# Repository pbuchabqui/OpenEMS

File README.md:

# OpenEMS

ECU para motores a combustao interna, focada no STM32H562RGT6 (Cortex-M33, C++17). Prioriza baixa latencia, baixo jitter e previsibilidade temporal para injecao, ignicao, sensores e calibracao.

Regras de codigo, gates de qualidade e errata: ver `CLAUDE.md`.

## Build

```bash
make firmware     # .elf/.hex/.bin em /tmp/openems-build
make host-test    # regressao no PC
make ci-local     # todos os gates antes de merge
make clean
```

## Instalacao no motor

Pelo dashboard proprio (`tools/openems_dash`, aba **Install**), com guia passo a passo; alternativa: TunerStudio com `tools/ts/openems.ini`.

## Documentacao

| Documento | Conteudo |
|---|---|
| `docs/bench_test_manual.md` | Teste de bancada na WeAct VGT6, sem atuadores |
| `docs/bench_report_template.md` | Modelo do relatório de bancada (preencher durante o ensaio) |
| `docs/hw/README.md` | Hardware e pinout |
| `docs/wiring_diagram.md` | Esquematicos eletricos |
| `docs/ROADMAP.md` | Backlog, progresso e histórico do que foi concluído |
| `docs/datalog.md` | Datalog em cartão SD (VGT6): formato, anel e ferramentas |
| `docs/nn_viabilidade.md` | Estudo: redes neurais no STM32H562 (X-τ, STFT, PID) |
| `docs/guia_instalacao.md` | Guia de instalação no motor (10 passos) |
| `docs/arquitetura.md` | Camadas, regras e contratos entre elas |
| `docs/pipeline_motor.md` | Captura CKP/CMP, combustível, ignição, scheduling, ADC, comunicação |
| `docs/errata_stm32h562.md` | Errata ES0565 e impactos no projeto |
| `docs/qualidade_e_testes.md` | Gates locais, layout dos testes host, segredos |
| `docs/mvp_bancada.md` | Definição de pronto da bancada, frames CAN, ETB, X-τ |
| `docs/estado_e_hardening.md` | Estado atual, hardening feito e pinout por placa |
| `docs/fueling_system.md`, `closed_loop_fuel.md`, `idle_system.md`, `ignition_system.md`, `protection_system.md`, `output_contract.md` | Subsistemas |

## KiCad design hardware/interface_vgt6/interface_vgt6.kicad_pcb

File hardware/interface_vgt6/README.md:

# Carrier VGT6 (`interface_vgt6/`)

> **Status:** vigente · validado 2026-11-23 (esquemático gerado e conferido com `kicad-cli` 10.0.7; sem PCB)

Esquemático KiCad 10 de 5 folhas (alimentação, saídas INJ/IGN, ETB e auxiliares, entradas, CAN e headers) da carrier que recebe a WeAct H562 VGT6. Especificação: `docs/hw/interface_vgt6.md` e `docs/hw/interface_vgt6_nets.md`. Abra `interface_vgt6.kicad_pro` no KiCad.

## Arquivos

- `interface_vgt6.kicad_sch` (raiz) e `power`, `outputs`, `etb_aux`, `inputs`, `comms` (`.kicad_sch`).
- `OpenEMS.kicad_sym` e `sym-lib-table`: símbolos do MAX9924 e do TPS2553, que a biblioteca oficial não tem.
- `gen/build.py`, `gen/kicadgen.py`: gerador.

## Regenerar

`python3 hardware/interface_vgt6/gen/build.py`. **O gerador é de uma passada**: ele reescreve todos os `.kicad_sch`, então depois de editar no KiCad não rode de novo sobre os mesmos arquivos.

## Conferir

```bash
kicad-cli sch erc hardware/interface_vgt6/interface_vgt6.kicad_sch
python3 tools/interface_netcheck.py
```

O `interface_netcheck.py` compara os pinos de P1/P2 da netlist com `docs/hw/interface_vgt6_nets.md` e `docs/hw/weact_h562_schematic.md`, e exige `PGND` e `SGND` separadas.

## Em aberto

Footprints, valores e posições dos componentes ainda são de projeto; não há PCB nem BOM fechada.

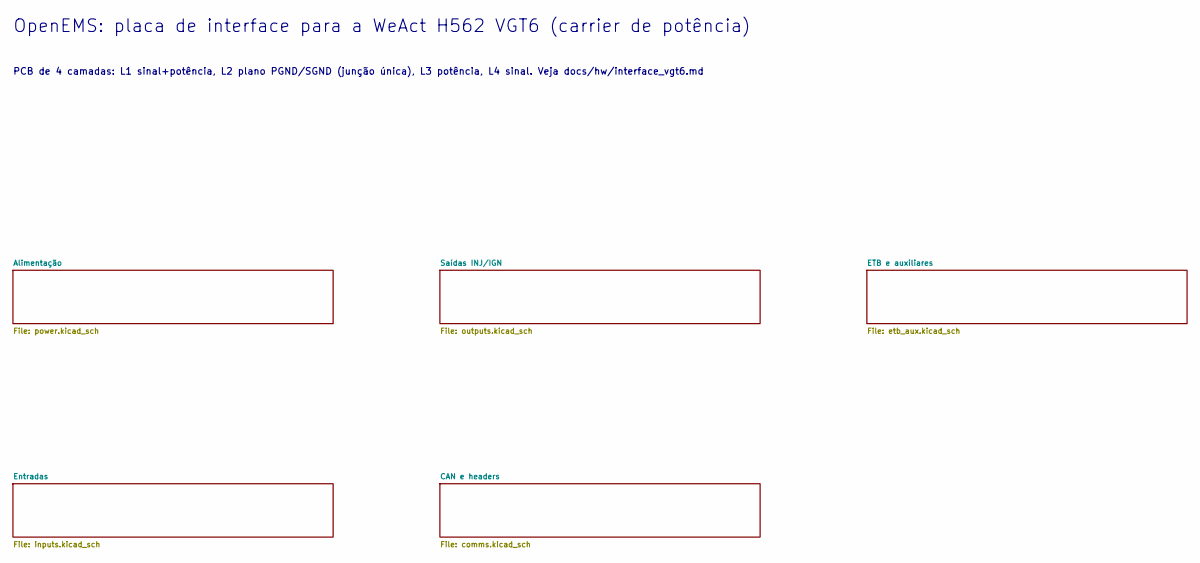
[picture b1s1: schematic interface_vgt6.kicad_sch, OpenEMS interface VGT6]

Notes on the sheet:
OpenEMS: placa de interface para a WeAct H562 VGT6 (carrier de potência)
PCB de 4 camadas: L1 sinal+potência, L2 plano PGND/SGND (junção única), L3 potência, L4 sinal. Veja docs/hw/interface_vgt6.md

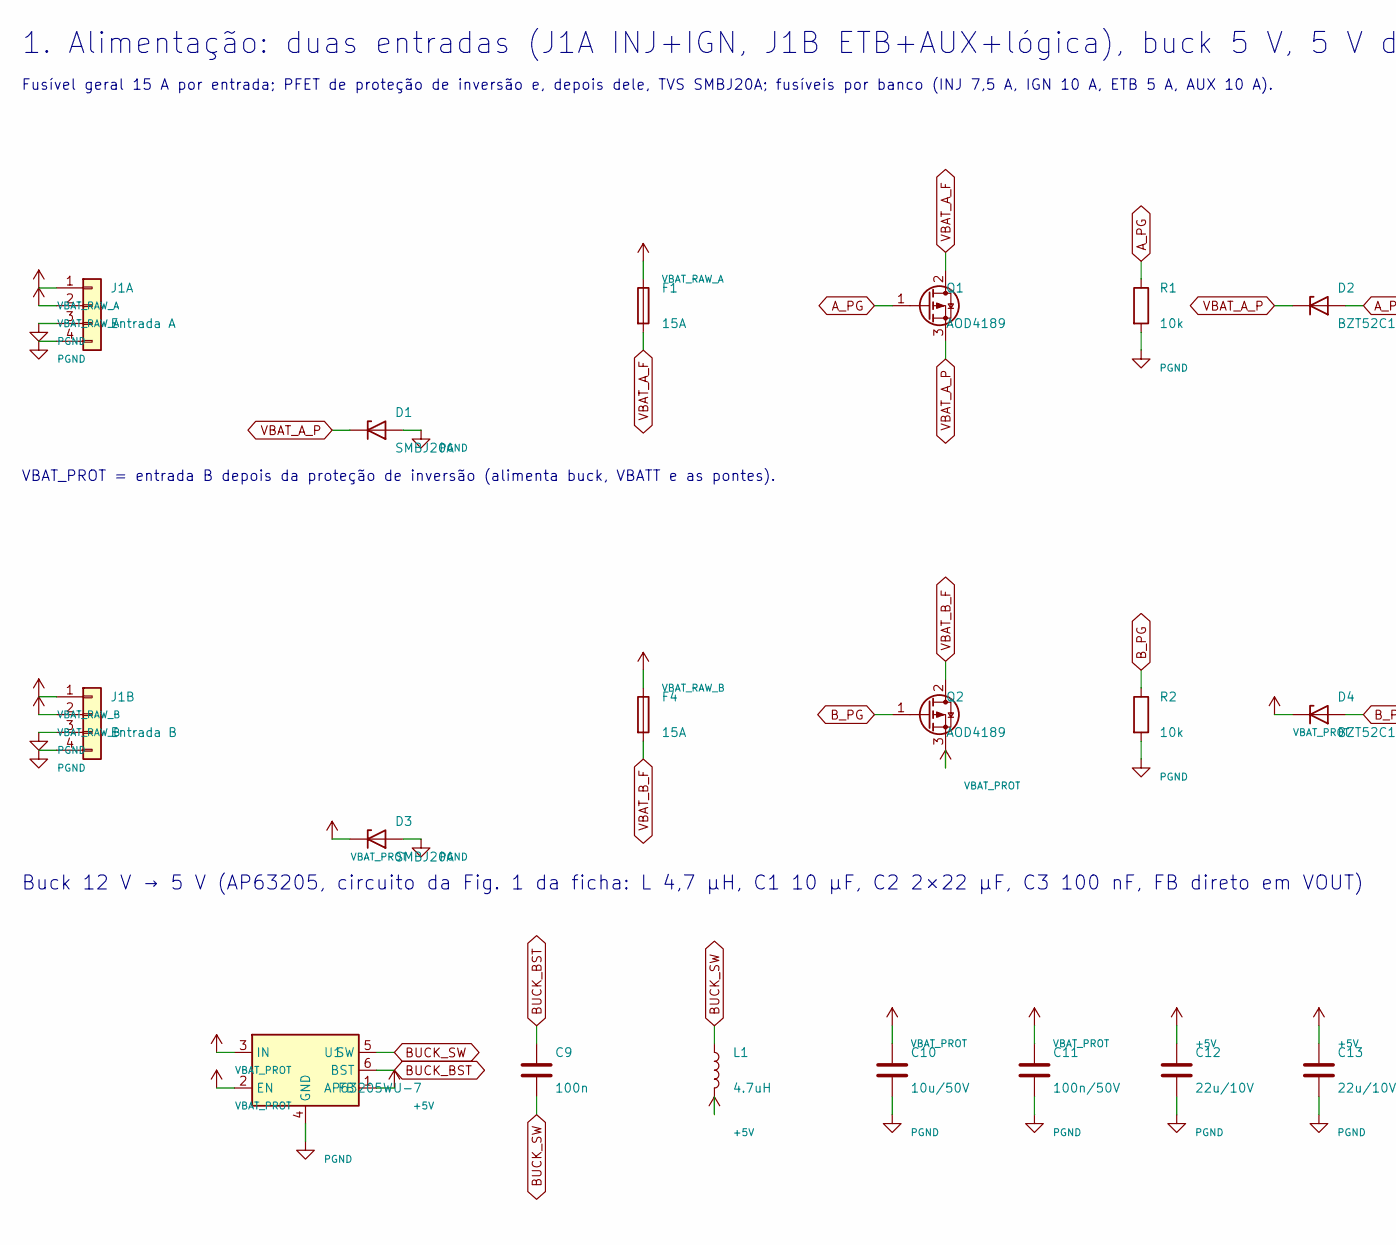
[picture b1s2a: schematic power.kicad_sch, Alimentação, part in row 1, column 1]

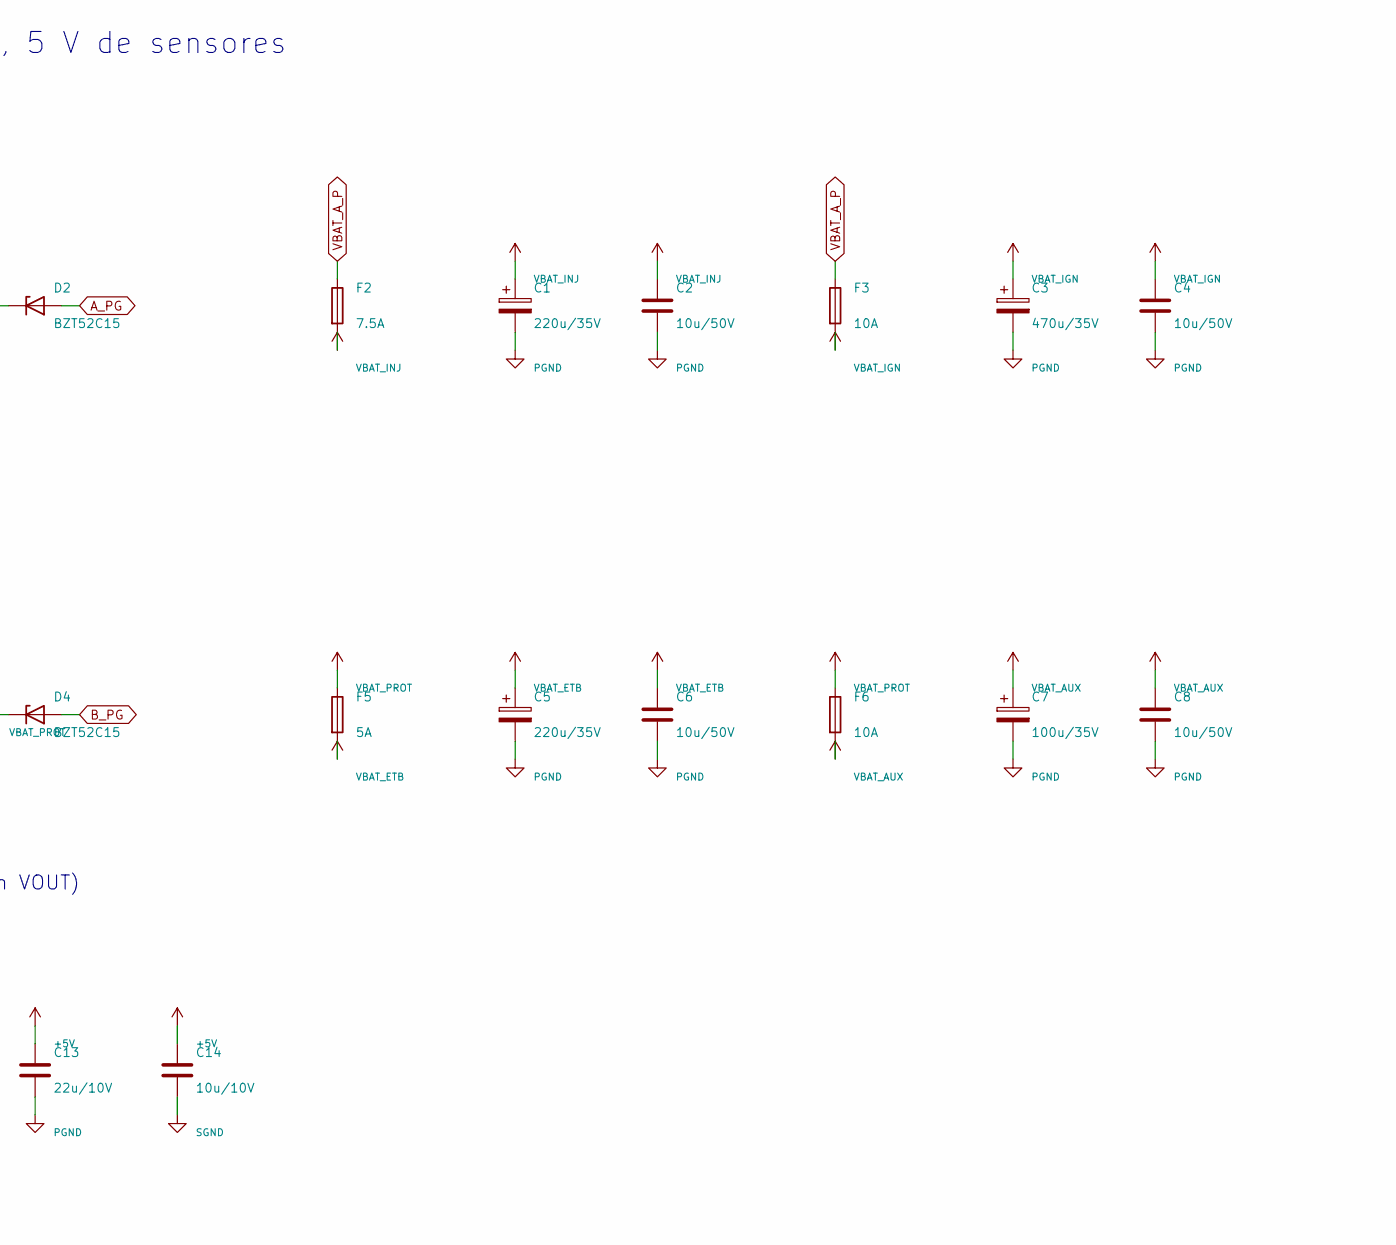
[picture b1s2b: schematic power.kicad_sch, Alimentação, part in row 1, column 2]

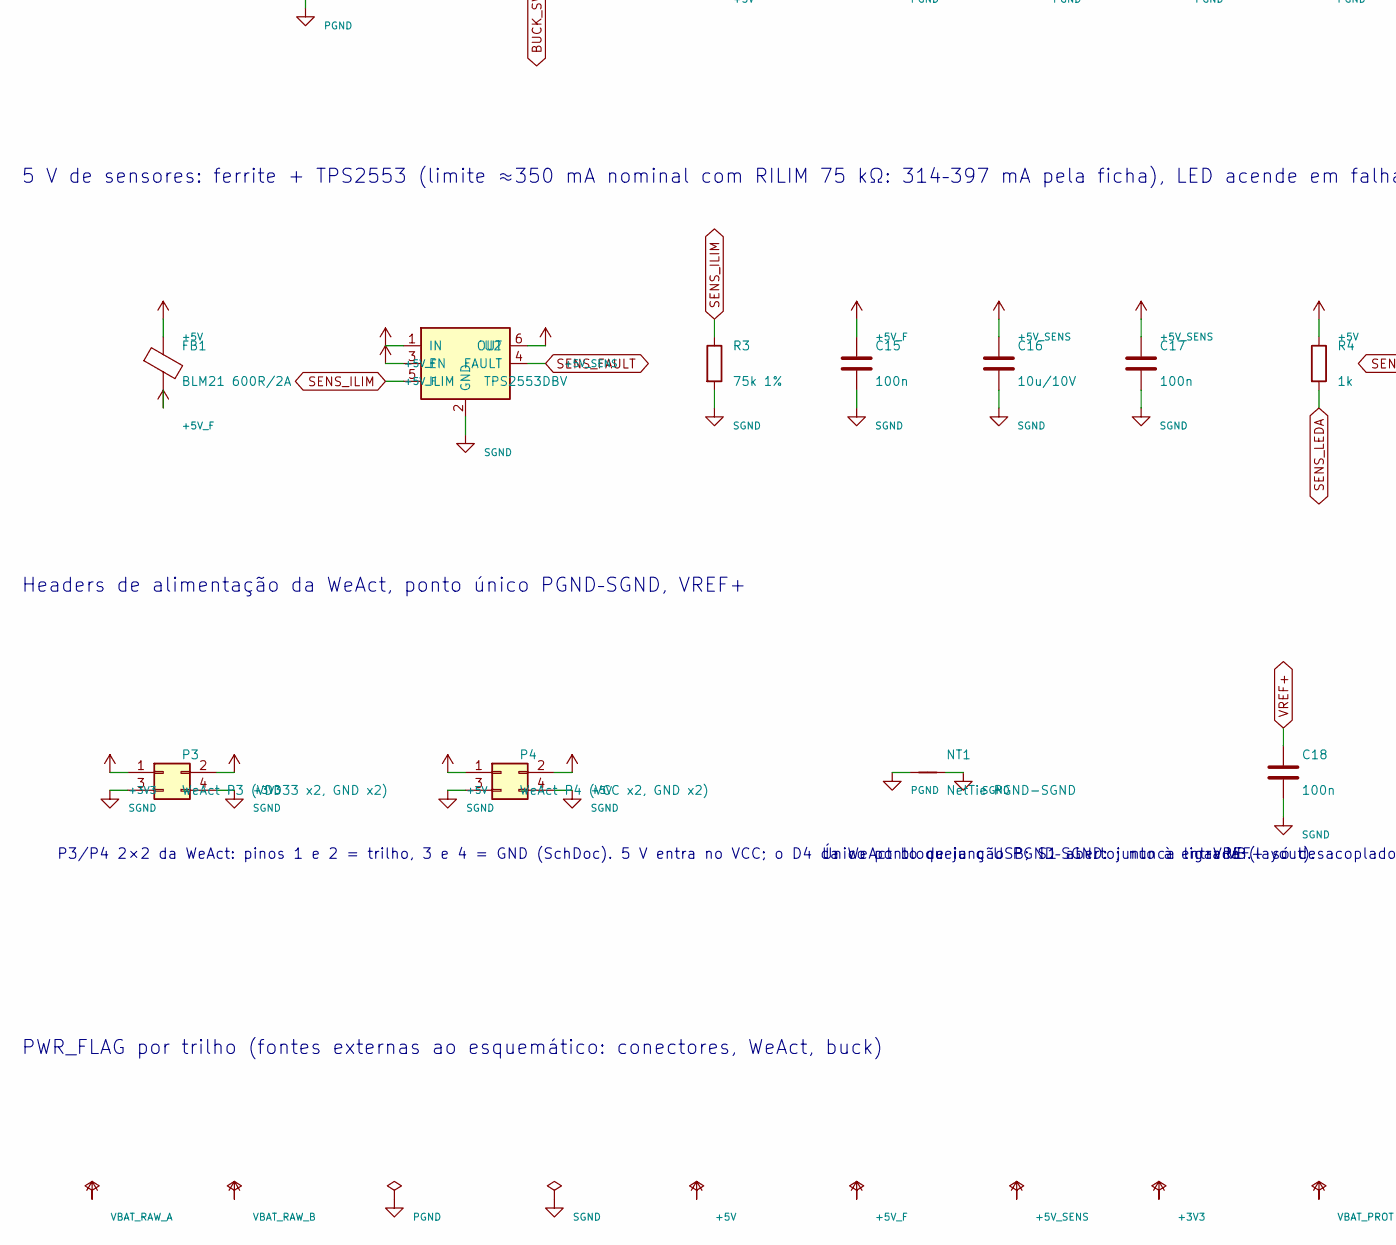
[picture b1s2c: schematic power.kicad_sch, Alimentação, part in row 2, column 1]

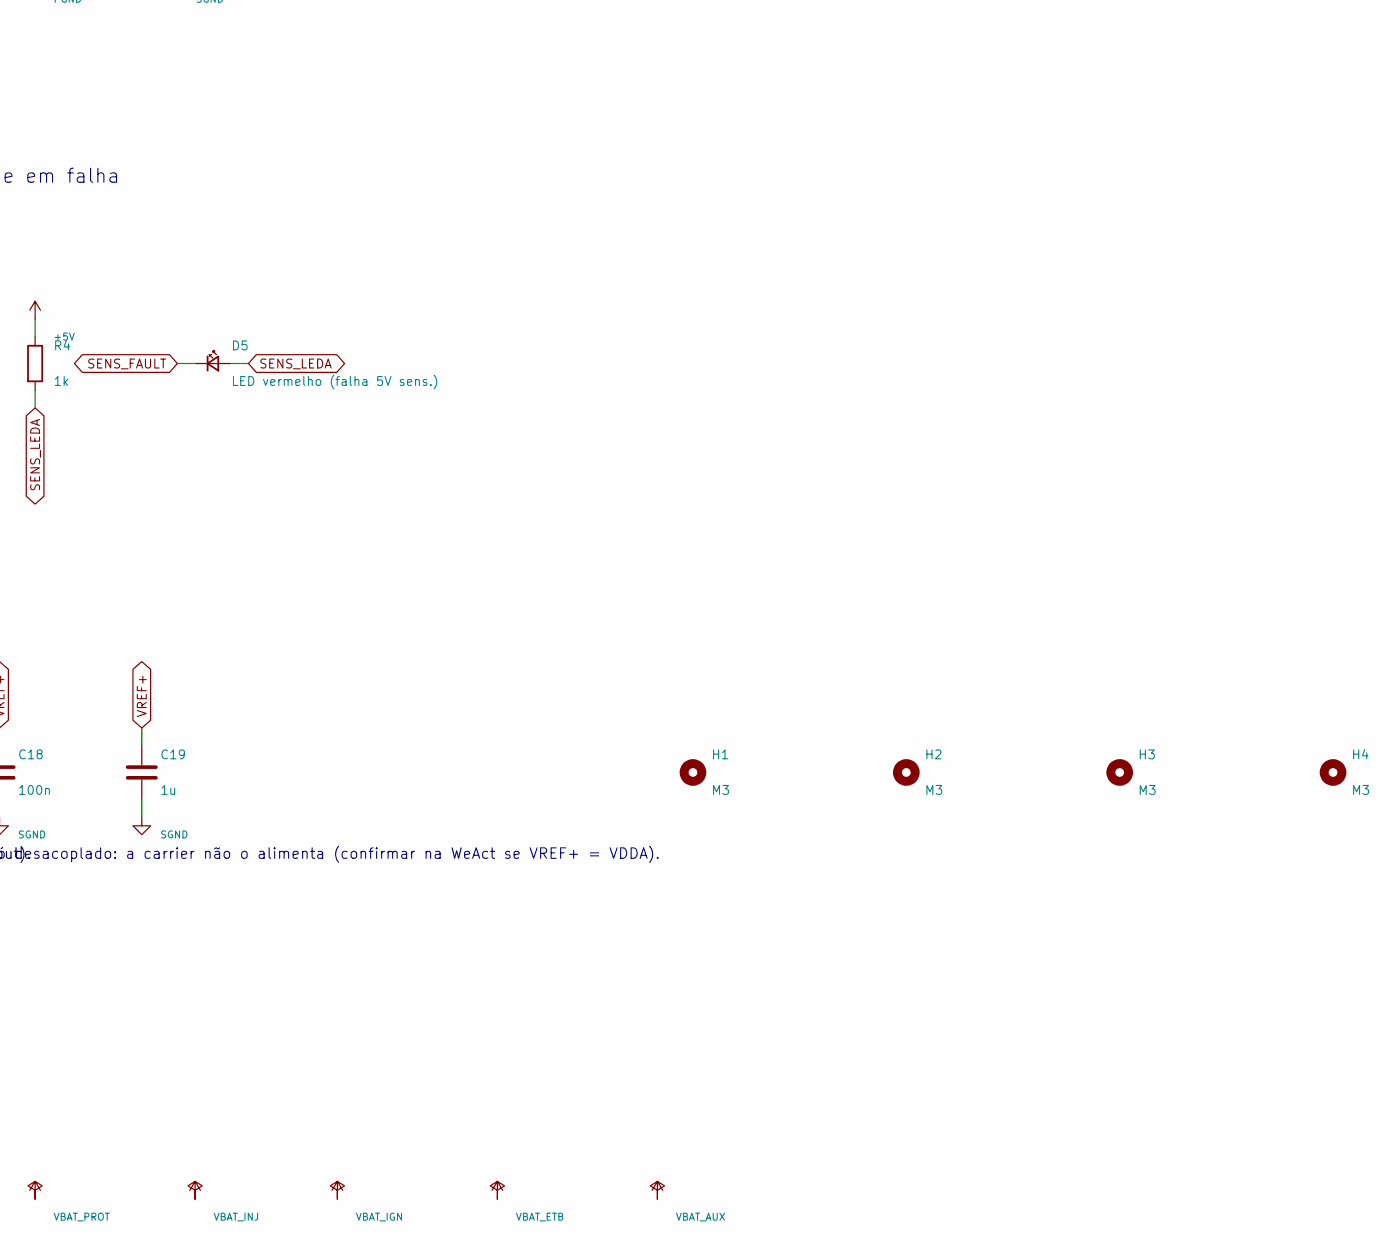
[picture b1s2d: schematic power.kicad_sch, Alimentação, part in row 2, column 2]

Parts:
C1, C5: 220u/35V; CP_Elec_8x10
C2, C4, C6, C8, C10: 10u/50V; C_1206_3216Metric
C3: 470u/35V; CP_Elec_10x10.5
C7: 100u/35V; CP_Elec_8x10
C9, C15, C17, C18: 100n; C_0603_1608Metric
C11: 100n/50V; C_0603_1608Metric
C12, C13: 22u/10V; C_0805_2012Metric
C14, C16: 10u/10V; C_0805_2012Metric
C19: 1u; C_0603_1608Metric
D1, D3: SMBJ20A; D_SMB
D2, D4: BZT52C15; D_SOD-123
D5: LED vermelho (falha 5V sens.); LED_0603_1608Metric
F1, F4: 15A; Fuseholder_Blade_ATO_Littelfuse_Pudenz_2_Pin
F2: 7.5A; Fuseholder_Blade_Mini_Keystone_3568
F3, F6: 10A; Fuseholder_Blade_Mini_Keystone_3568
F5: 5A; Fuseholder_Blade_Mini_Keystone_3568
FB1: BLM21 600R/2A; L_0805_2012Metric
H1, H2, H3, H4: M3; MountingHole_3.2mm_M3
J1A: Entrada A; PhoenixContact_MSTBA_2,5_4-G-5,08_1x04_P5.08mm_Horizontal
J1B: Entrada B; PhoenixContact_MSTBA_2,5_4-G-5,08_1x04_P5.08mm_Horizontal
L1: 4.7uH; L_Bourns_SRP7028A_7.3x6.6mm
NT1: NetTie PGND-SGND; NetTie-2_SMD_Pad0.5mm
P3: WeAct P3 (VDD33 x2, GND x2); PinHeader_2x02_P2.54mm_Vertical
P4: WeAct P4 (VCC x2, GND x2); PinHeader_2x02_P2.54mm_Vertical
Q1, Q2: AOD4189; TO-252-3_TabPin2
R1, R2: 10k; R_0603_1608Metric
R3: 75k 1%; R_0603_1608Metric
R4: 1k; R_0603_1608Metric
U1: AP63205WU-7; TSOT-23-6
U2: TPS2553DBV; SOT-23-6

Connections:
+3V3: P3.1, P3.2; also elsewhere on the board
+5V: C12.1, C13.1, C14.1, FB1.1, L1.2, P4.1, P4.2, R4.1, U1.1 (FB); also elsewhere on the board
+5V_F: C15.1, FB1.2, U2.1 (IN), U2.3 (EN)
+5V_SENS: C16.1, C17.1, U2.6 (OUT); also elsewhere on the board
A_PG: D2.2 (A), Q1.1 (G), R1.1
BUCK_BST: C9.1, U1.6 (BST)
BUCK_SW: C9.2, L1.1, U1.5 (SW)
B_PG: D4.2 (A), Q2.1 (G), R2.1
PGND: C1.2, C2.2, C3.2, C4.2, C5.2, C6.2, C7.2, C8.2, C10.2, C11.2, C12.2, C13.2, D1.2 (A), D3.2 (A), J1A.3, J1A.4, J1B.3, J1B.4, NT1.1, R1.2, R2.2, U1.4 (GND); also elsewhere on the board
SENS_FAULT: D5.1 (K), U2.4 (FAULT)
SENS_ILIM: R3.1, U2.5 (ILIM)
SENS_LEDA: D5.2 (A), R4.2
SGND: C14.2, C15.2, C16.2, C17.2, C18.2, C19.2, NT1.2, P3.3, P3.4, P4.3, P4.4, R3.2, U2.2 (GND); also elsewhere on the board
VBAT_AUX: C7.1, C8.1, F6.2; also elsewhere on the board
VBAT_A_F: F1.2, Q1.2 (D)
VBAT_A_P: D1.1 (K), D2.1 (K), F2.1, F3.1, Q1.3 (S)
VBAT_B_F: F4.2, Q2.2 (D)
VBAT_ETB: C5.1, C6.1, F5.2; also elsewhere on the board
VBAT_IGN: C3.1, C4.1, F3.2; also elsewhere on the board
VBAT_INJ: C1.1, C2.1, F2.2; also elsewhere on the board
VBAT_PROT: C10.1, C11.1, D3.1 (K), D4.1 (K), F5.1, F6.1, Q2.3 (S), U1.2 (EN), U1.3 (IN); also elsewhere on the board
VBAT_RAW_A: F1.1, J1A.1, J1A.2
VBAT_RAW_B: F4.1, J1B.1, J1B.2
VREF+: C18.1, C19.1; also elsewhere on the board

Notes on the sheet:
1. Alimentação: duas entradas (J1A INJ+IGN, J1B ETB+AUX+lógica), buck 5 V, 5 V de sensores
Fusível geral 15 A por entrada; PFET de proteção de inversão e, depois dele, TVS SMBJ20A; fusíveis por banco (INJ 7,5 A, IGN 10 A, ETB 5 A, AUX 10 A).
VBAT_PROT = entrada B depois da proteção de inversão (alimenta buck, VBATT e as pontes).
Buck 12 V → 5 V (AP63205, circuito da Fig. 1 da ficha: L 4,7 µH, C1 10 µF, C2 2×22 µF, C3 100 nF, FB direto em VOUT)
5 V de sensores: ferrite + TPS2553 (limite ≈350 mA nominal com RILIM 75 kΩ: 314–397 mA pela ficha), LED acende em falha
Headers de alimentação da WeAct, ponto único PGND–SGND, VREF+
P3/P4 2×2 da WeAct: pinos 1 e 2 = trilho, 3 e 4 = GND (SchDoc). 5 V entra no VCC; o D4 da WeAct bloqueia o USB; S1 aberto; nunca ligar VB.
Único ponto de junção PGND–SGND: junto à entrada (layout).
VREF+ só desacoplado: a carrier não o alimenta (confirmar na WeAct se VREF+ = VDDA).
PWR_FLAG por trilho (fontes externas ao esquemático: conectores, WeAct, buck)

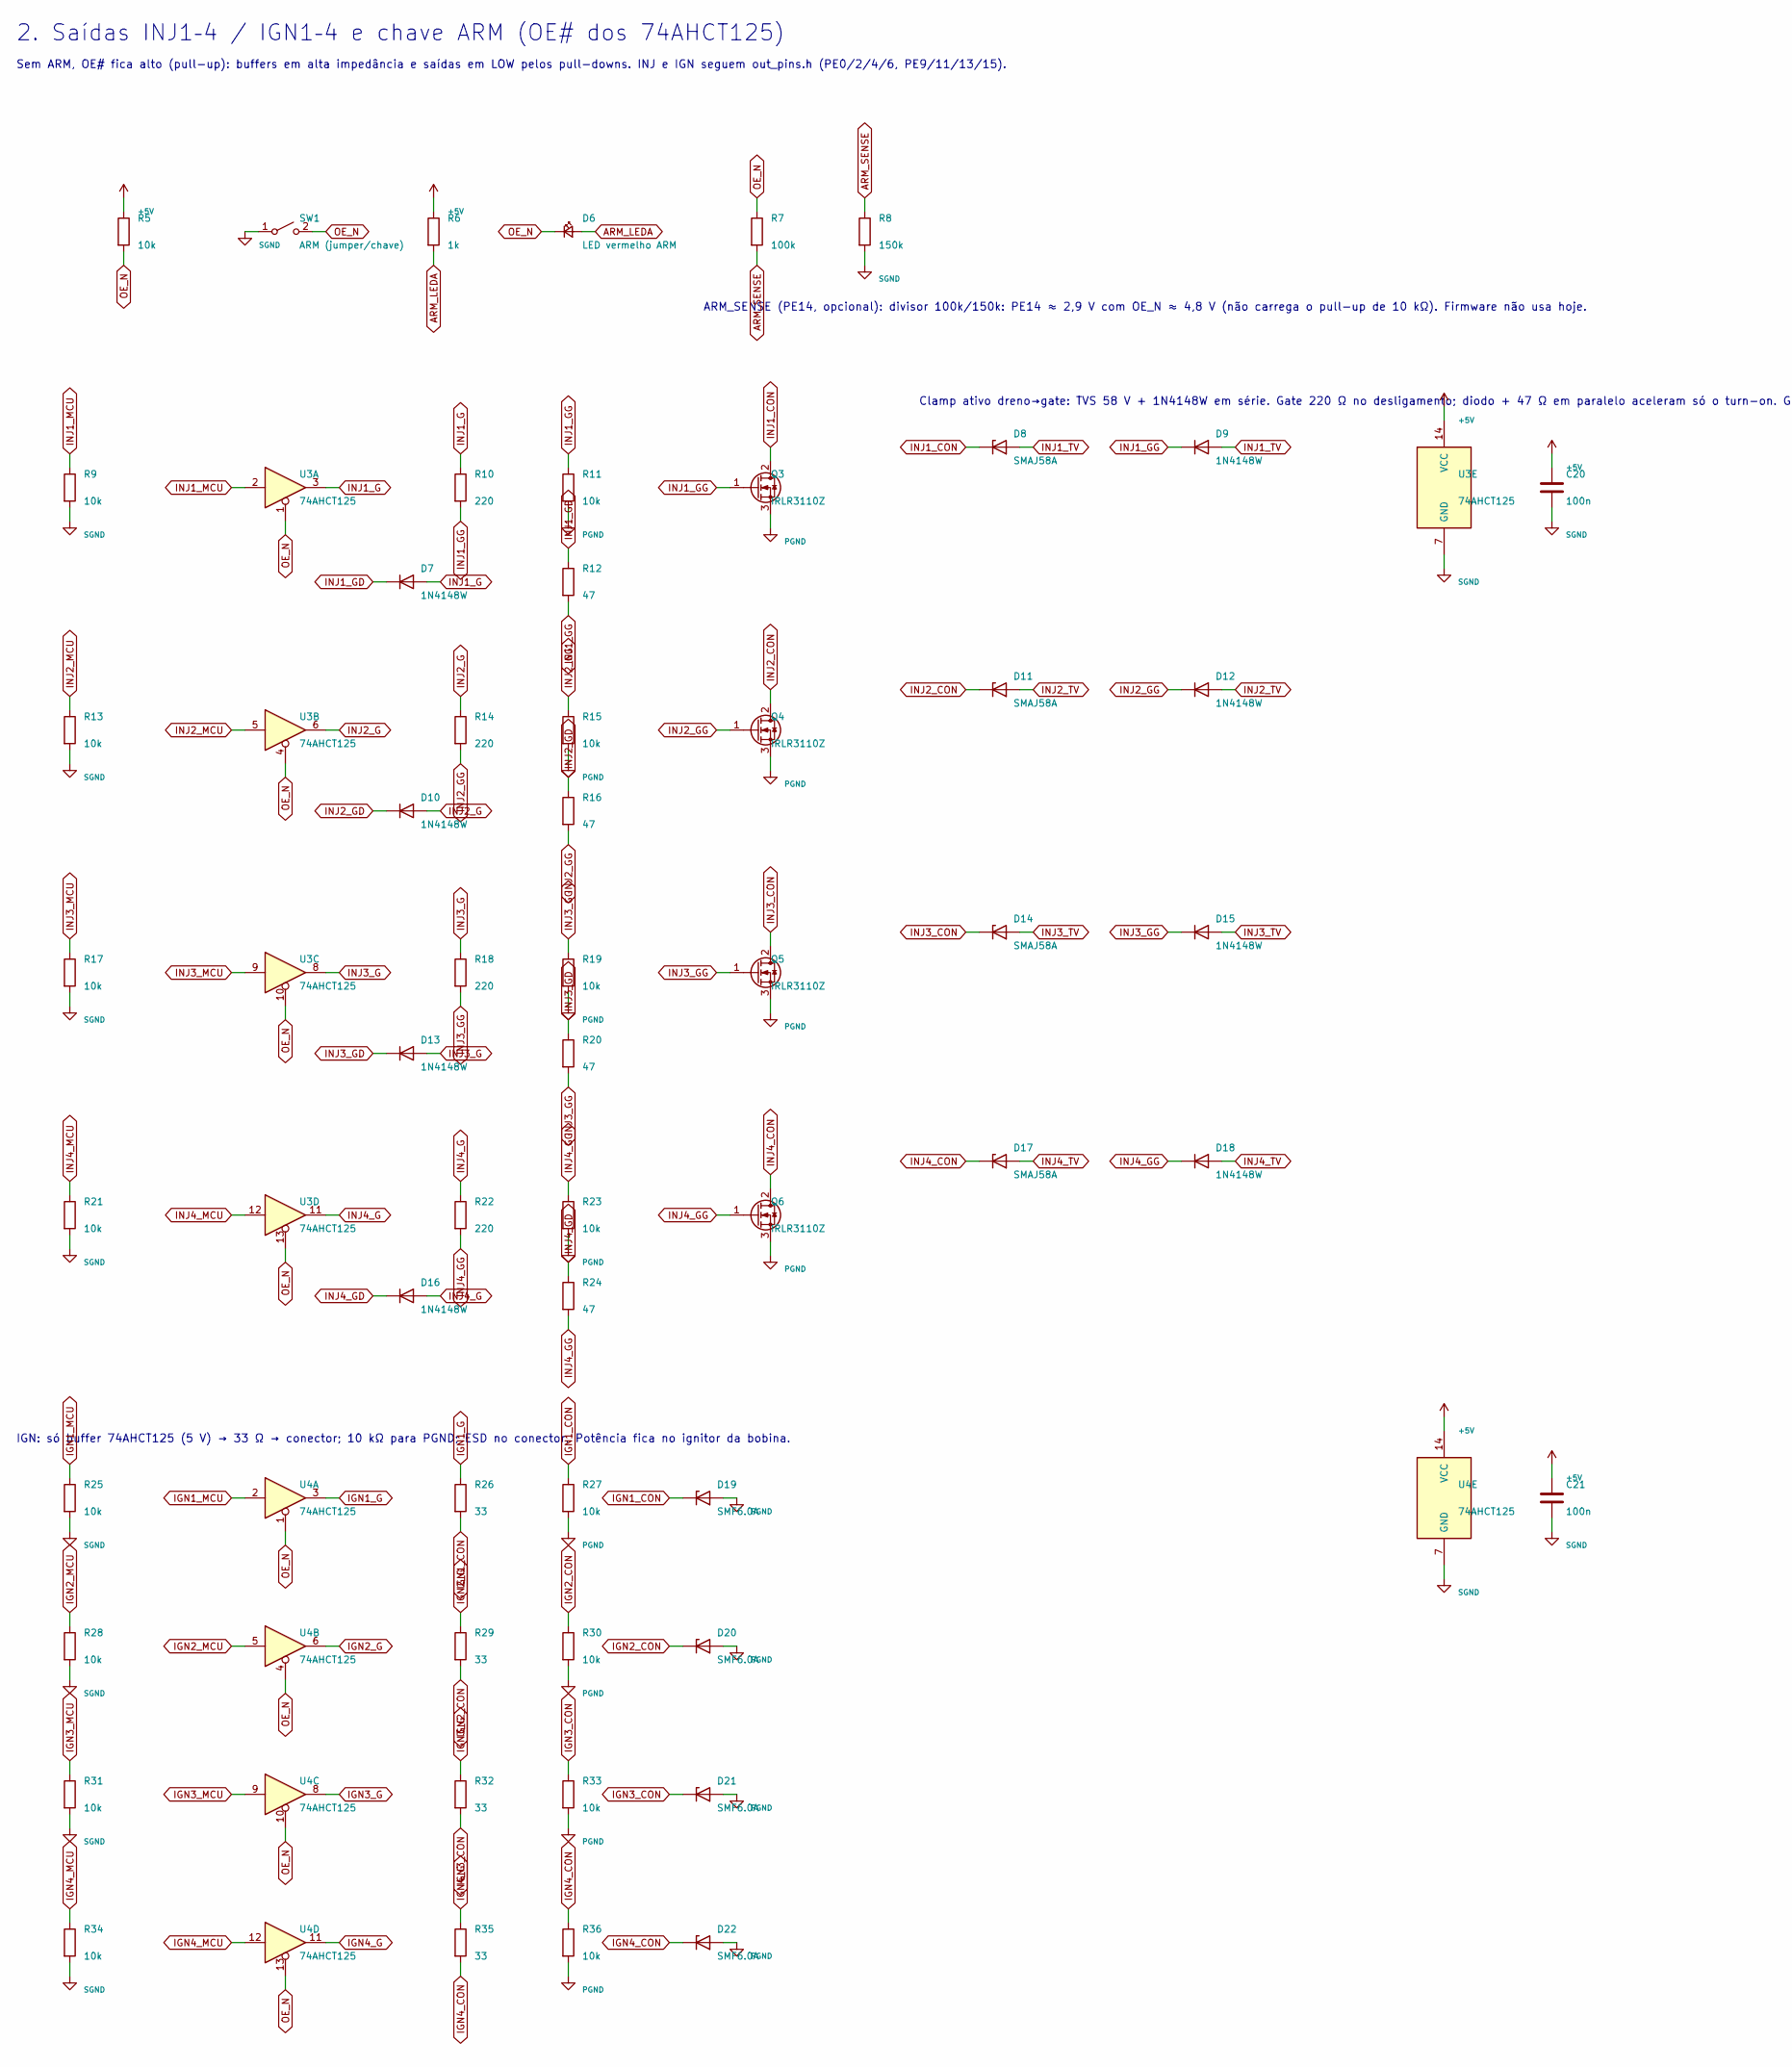
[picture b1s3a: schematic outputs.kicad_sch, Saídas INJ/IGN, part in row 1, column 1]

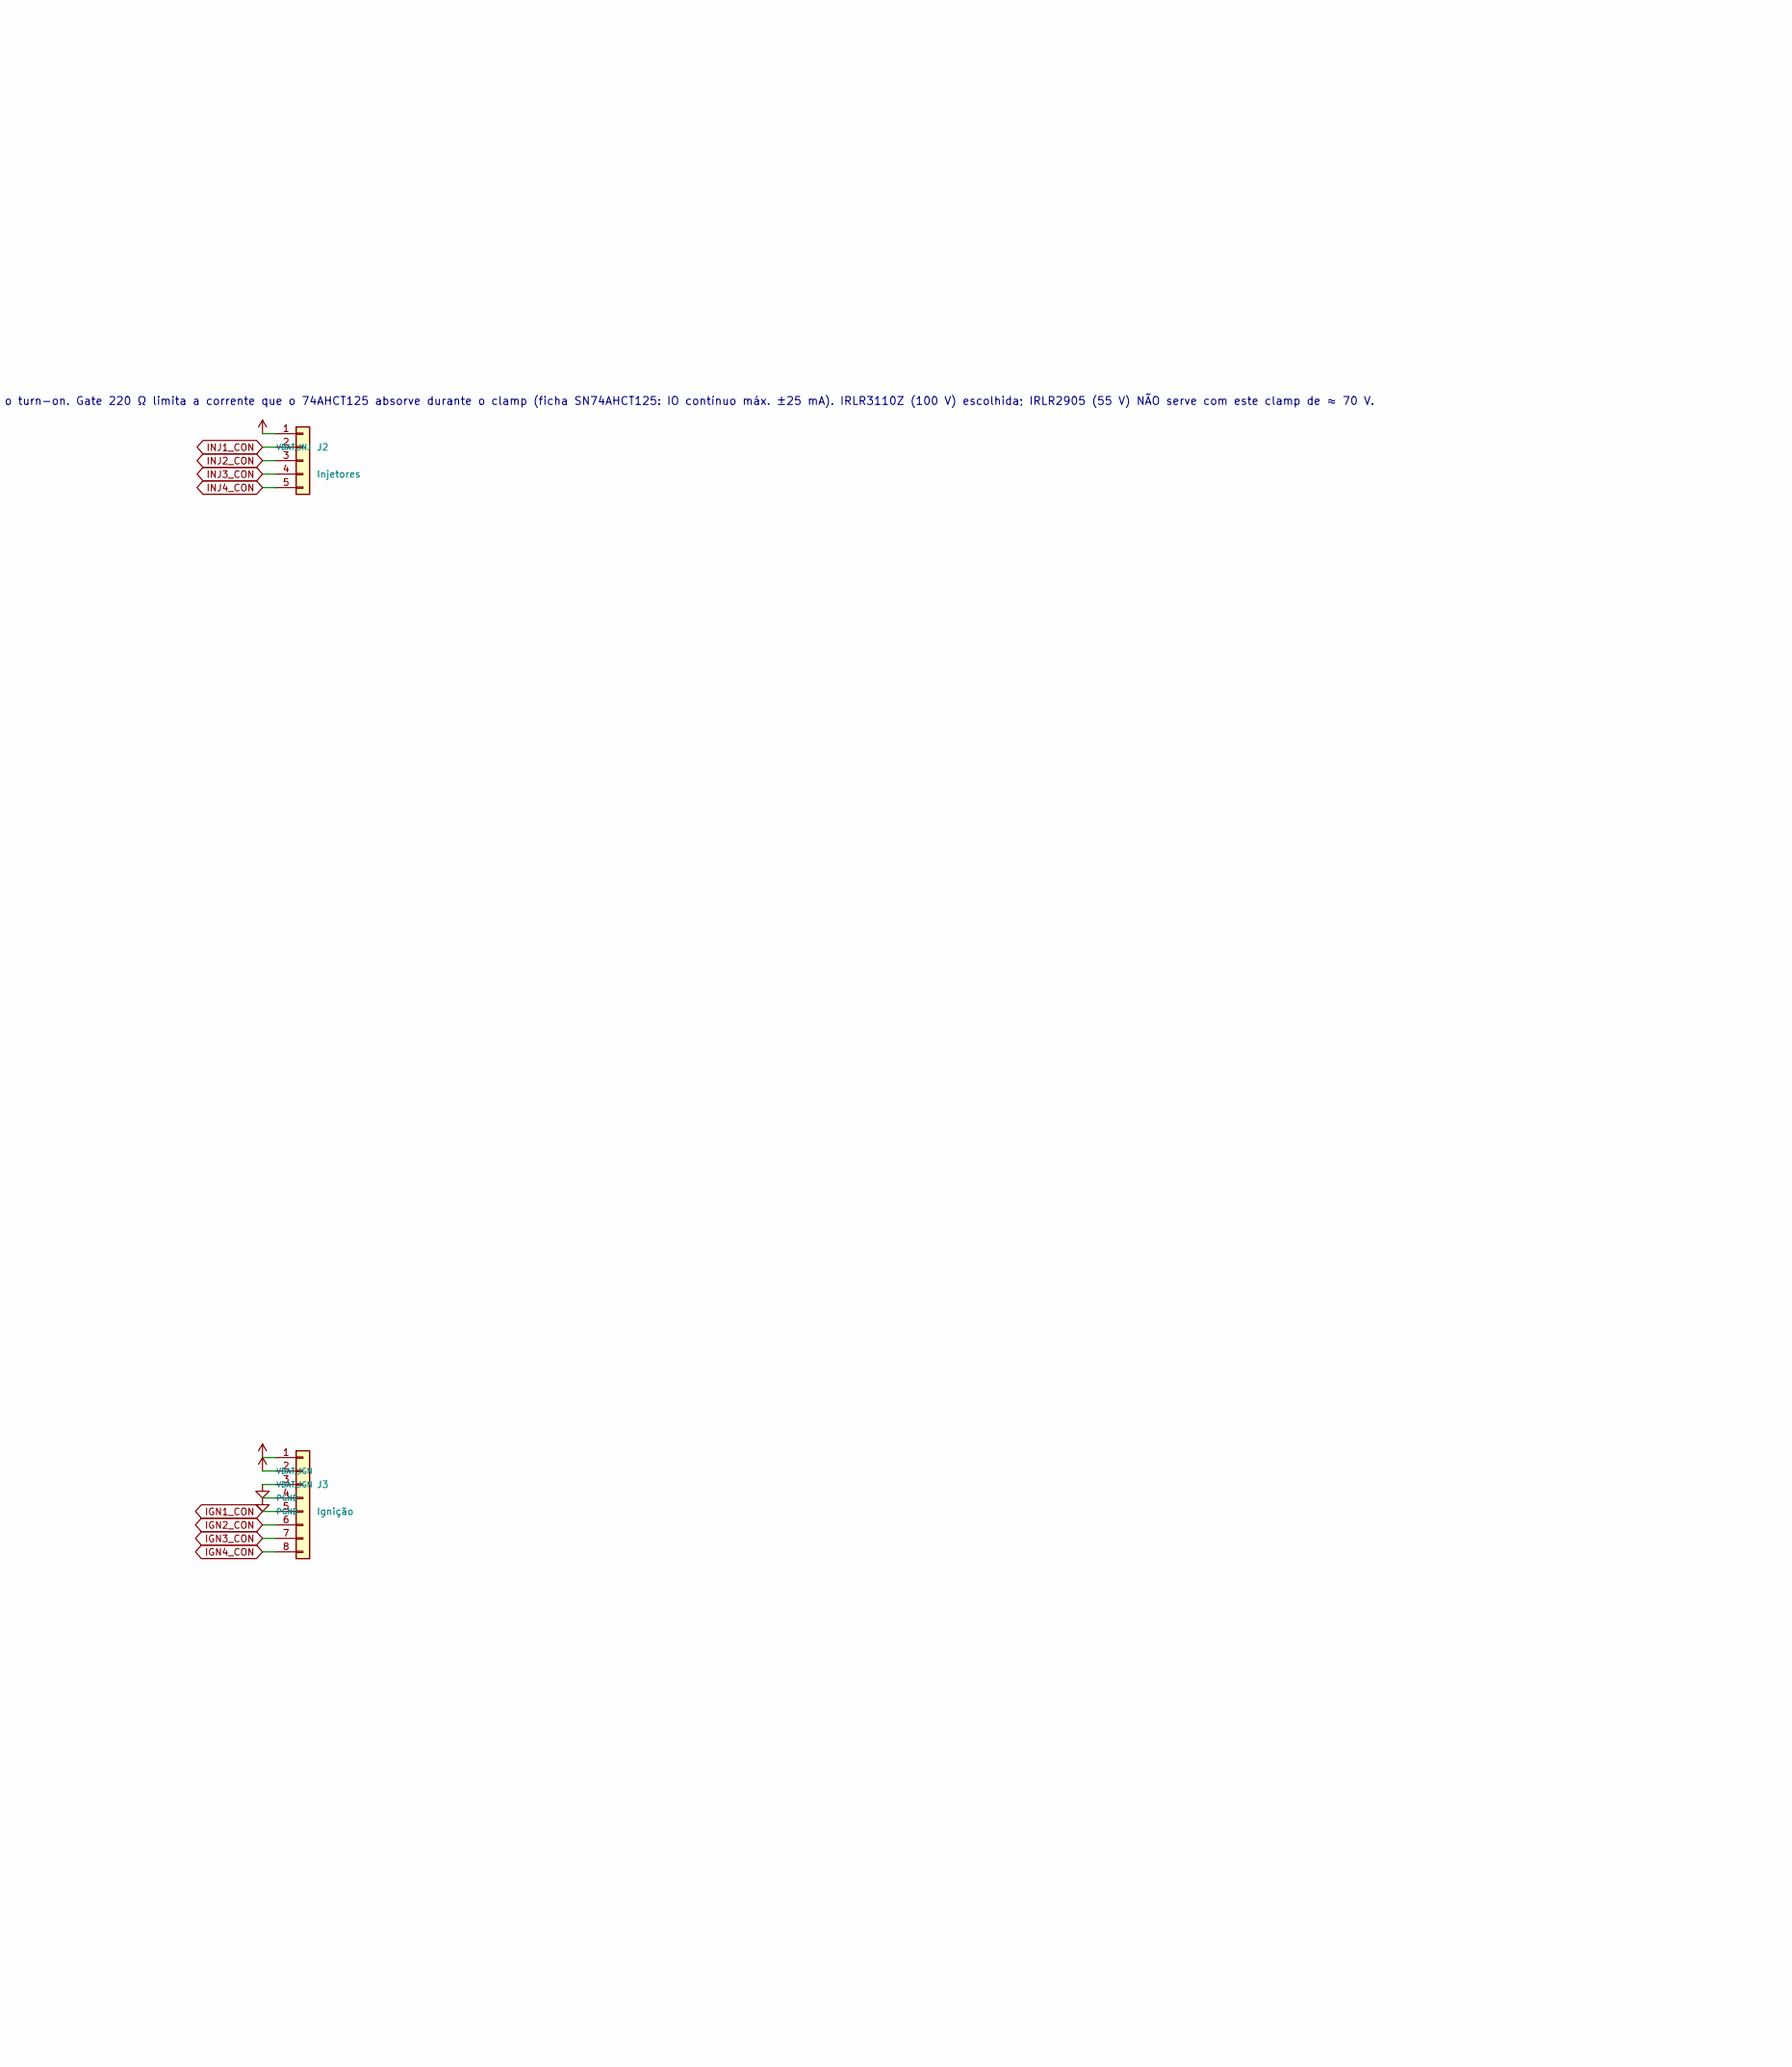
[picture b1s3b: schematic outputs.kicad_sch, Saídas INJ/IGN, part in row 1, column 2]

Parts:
C20, C21: 100n; C_0603_1608Metric
D6: LED vermelho ARM; LED_0603_1608Metric
D7, D9, D10, D12, D13, D15, D16, D18: 1N4148W; D_SOD-123
D8, D11, D14, D17: SMAJ58A; D_SMA
D19, D20, D21, D22: SMF6.0A; D_SOD-123F
J2: Injetores; PhoenixContact_MSTBA_2,5_5-G-5,08_1x05_P5.08mm_Horizontal
J3: Ignição; PhoenixContact_MSTBA_2,5_8-G-5,08_1x08_P5.08mm_Horizontal
Q3, Q4, Q5, Q6: IRLR3110Z; TO-252-3_TabPin2
R5, R9, R11, R13, R15, R17, R19, R21, R23, R25, R27, R28, R30, R31, R33, R34, R36: 10k; R_0603_1608Metric
R6: 1k; R_0603_1608Metric
R7: 100k; R_0603_1608Metric
R8: 150k; R_0603_1608Metric
R10, R14, R18, R22: 220; R_0603_1608Metric
R12, R16, R20, R24: 47; R_0603_1608Metric
R26, R29, R32, R35: 33; R_0603_1608Metric
SW1: ARM (jumper/chave); PinHeader_1x02_P2.54mm_Vertical
U3, U4: 74AHCT125; TSSOP-14_4.4x5mm_P0.65mm

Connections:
+5V: C20.1, C21.1, R5.1, R6.1, U3.14 (VCC), U4.14 (VCC); also elsewhere on the board
ARM_LEDA: D6.2 (A), R6.2
ARM_SENSE: R7.2, R8.1; also elsewhere on the board
IGN1_CON: D19.1 (K), J3.5, R26.2, R27.1
IGN1_G: R26.1, U4.3
IGN1_MCU: R25.1, U4.2; also elsewhere on the board
IGN2_CON: D20.1 (K), J3.6, R29.2, R30.1
IGN2_G: R29.1, U4.6
IGN2_MCU: R28.1, U4.5; also elsewhere on the board
IGN3_CON: D21.1 (K), J3.7, R32.2, R33.1
IGN3_G: R32.1, U4.8
IGN3_MCU: R31.1, U4.9; also elsewhere on the board
IGN4_CON: D22.1 (K), J3.8, R35.2, R36.1
IGN4_G: R35.1, U4.11
IGN4_MCU: R34.1, U4.12; also elsewhere on the board
INJ1_CON: D8.1 (K), J2.2, Q3.2 (D)
INJ1_G: D7.2 (A), R10.1, U3.3
INJ1_GD: D7.1 (K), R12.1
INJ1_GG: D9.1 (K), Q3.1 (G), R10.2, R11.1, R12.2
INJ1_MCU: R9.1, U3.2; also elsewhere on the board
INJ1_TV: D8.2 (A), D9.2 (A)
INJ2_CON: D11.1 (K), J2.3, Q4.2 (D)
INJ2_G: D10.2 (A), R14.1, U3.6
INJ2_GD: D10.1 (K), R16.1
INJ2_GG: D12.1 (K), Q4.1 (G), R14.2, R15.1, R16.2
INJ2_MCU: R13.1, U3.5; also elsewhere on the board
INJ2_TV: D11.2 (A), D12.2 (A)
INJ3_CON: D14.1 (K), J2.4, Q5.2 (D)
INJ3_G: D13.2 (A), R18.1, U3.8
INJ3_GD: D13.1 (K), R20.1
INJ3_GG: D15.1 (K), Q5.1 (G), R18.2, R19.1, R20.2
INJ3_MCU: R17.1, U3.9; also elsewhere on the board
INJ3_TV: D14.2 (A), D15.2 (A)
INJ4_CON: D17.1 (K), J2.5, Q6.2 (D)
INJ4_G: D16.2 (A), R22.1, U3.11
INJ4_GD: D16.1 (K), R24.1
INJ4_GG: D18.1 (K), Q6.1 (G), R22.2, R23.1, R24.2
INJ4_MCU: R21.1, U3.12; also elsewhere on the board
INJ4_TV: D17.2 (A), D18.2 (A)
OE_N: D6.1 (K), R5.2, R7.1, SW1.2 (B), U3.1, U3.4, U3.10, U3.13, U4.1, U4.4, U4.10, U4.13; also elsewhere on the board
PGND: D19.2 (A), D20.2 (A), D21.2 (A), D22.2 (A), J3.3, J3.4, Q3.3 (S), Q4.3 (S), Q5.3 (S), Q6.3 (S), R11.2, R15.2, R19.2, R23.2, R27.2, R30.2, R33.2, R36.2; also elsewhere on the board
SGND: C20.2, C21.2, R8.2, R9.2, R13.2, R17.2, R21.2, R25.2, R28.2, R31.2, R34.2, SW1.1 (A), U3.7 (GND), U4.7 (GND); also elsewhere on the board
VBAT_IGN: J3.1, J3.2; also elsewhere on the board
VBAT_INJ: J2.1; also elsewhere on the board

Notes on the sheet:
2. Saídas INJ1–4 / IGN1–4 e chave ARM (OE# dos 74AHCT125)
Sem ARM, OE# fica alto (pull-up): buffers em alta impedância e saídas em LOW pelos pull-downs. INJ e IGN seguem out_pins.h (PE0/2/4/6, PE9/11/13/15).
ARM_SENSE (PE14, opcional): divisor 100k/150k: PE14 ≈ 2,9 V com OE_N ≈ 4,8 V (não carrega o pull-up de 10 kΩ). Firmware não usa hoje.
Clamp ativo dreno→gate: TVS 58 V + 1N4148W em série. Gate 220 Ω no desligamento; diodo + 47 Ω em paralelo aceleram só o turn-on. Gate 220 Ω limita a corrente que o 74AHCT125 absorve durante o clamp (ficha SN74AHCT125: IO contínuo máx. ±25 mA). IRLR3110Z (100 V) escolhida; IRLR2905 (55 V) NÃO serve 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
IGN: só buffer 74AHCT125 (5 V) → 33 Ω → conector; 10 kΩ para PGND; ESD no conector. Potência fica no ignitor da bobina.
